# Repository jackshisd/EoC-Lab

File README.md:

| Supported Targets | ESP32 | ESP32-P4 | ESP32-S3 |
| ----------------- | ----- | -------- | -------- |

# ESP32-S3 SD + Mic + OV2640 Recorder

__WARNING:__ This project writes audio/video files to the SD card. Back up your data before testing.

Records:
- **Audio**: WAV via I2S mic (ICS-43434), `mic_0001.wav`, `mic_0002.wav`, ...
- **Contact audio**: WAV via ES8388 contact mic board, `CT0001.WAV`, `CT0002.WAV`, ...
- **Video**: MJPEG via OV2640, `VID0001.MJP`, `VID0002.MJP`, ...

Core features:
- SDMMC FAT mount/unmount
- USB MSC to expose the SD card when idle
- SSD1306 I2C OLED status
- Button UI
- BLE scan trigger (advertisements) with timestamped filenames
- Simultaneous standard mic + contact mic recording to separate WAV files
- Boot-time ES8388 codec bring-up so contact recording does not reinitialize the codec on every session

Supports SD (SDSC, SDHC, SDXC) cards and eMMC.

## Quick wiring map (ESP32-S3)

- **SD card (SDMMC):**
  - CLK: GPIO6
  - CMD: GPIO7
  - D0: GPIO5
  - D1: GPIO4
  - D2: GPIO16
  - D3: GPIO15
- **Mic (I2S):**
  - BCLK: GPIO38
  - LRCK/WS: GPIO40
  - DOUT -> ESP DIN: GPIO39
- **OLED (I2C, addr `0x3C`):**
  - SDA: GPIO1
  - SCL: GPIO2
- **Contact mic codec board (ES8388 + MCP6002):**
  - I2C SDA: GPIO1
  - I2C SCL: GPIO2
  - MCLK: GPIO41
  - ASDOUT -> ESP DIN: GPIO42
  - SCLK/BCLK: GPIO43
  - LRCK/WS: GPIO44
- **Button:**
  - GPIO45
- **Camera (OV2640):**
  - SCCB SDA: GPIO18
  - SCCB SCL: GPIO17
  - XCLK: GPIO9 (10 MHz)
  - D0..D7: GPIO47, GPIO48, GPIO14, GPIO21, GPIO12, GPIO13, GPIO10, GPIO11
  - PCLK: GPIO46
  - VSYNC: GPIO3
  - HREF: GPIO8
  - PWDN/RESET: tied in hardware (disabled in software with `-1`)

## Hardware

This project targets ESP32-S3 and uses an SD card breakout or slot, an I2S mic, an SSD1306 OLED, and an OV2640 camera.

Although it is possible to connect an SD card breakout adapter, keep in mind that connections using breakout cables are often unreliable and have poor signal integrity. You may need to use lower clock frequency when working with SD card breakout adapters.

This project doesn't utilize card detect (CD) and write protect (WP) signals from SD card slot.

### Pin assignments for ESP32

On ESP32, SDMMC peripheral is connected to specific GPIO pins using the IO MUX. GPIO pins cannot be customized. Please see the table below for the pin connections.

When using an ESP-WROVER-KIT board, this example runs without any extra modifications required. Only an SD card needs to be inserted into the slot.

ESP32 pin     | SD card pin | Notes
--------------|-------------|------------
GPIO14 (MTMS) | CLK         | 10k pullup in SD mode
GPIO15 (MTDO) | CMD         | 10k pullup in SD mode
GPIO2         | D0          | 10k pullup in SD mode, pull low to go into download mode (see Note about GPIO2 below!)
GPIO4         | D1          | not used in 1-line SD mode; 10k pullup in 4-line SD mode
GPIO12 (MTDI) | D2          | not used in 1-line SD mode; 10k pullup in 4-line SD mode (see Note about GPIO12 below!)
GPIO13 (MTCK) | D3          | not used in 1-line SD mode, but card's D3 pin must have a 10k pullup

### Pin assignments for ESP32-S3 (current project)

On ESP32-S3, SDMMC peripheral is connected to GPIO pins using GPIO matrix. This allows arbitrary GPIOs to be used to connect an SD card. In this example, GPIOs can be configured in two ways:

1. Using menuconfig: Run `idf.py menuconfig` in the project directory and open "SD/MMC Example Configuration" menu.
2. In the source code: See the initialization of `sdmmc_slot_config_t slot_config` structure in the example code.

The table below lists the default pin assignments.

When using an ESP32-S3-USB-OTG board, this example runs without any extra modifications required. Only an SD card needs to be inserted into the slot.

ESP32-S3 pin  | SD card pin | Notes
--------------|-------------|------------
GPIO6         | CLK         | 10k pullup
GPIO7         | CMD         | 10k pullup
GPIO5         | D0          | 10k pullup
GPIO4         | D1          | 10k pullup
GPIO16        | D2          | 10k pullup
GPIO15        | D3          | 10k pullup (required even in 1-line mode)

### I2S mic (ICS-43434)

ESP32-S3 pin  | Mic pin
--------------|---------
GPIO38        | BCLK/SCK
GPIO40        | WS/LRCL
GPIO39        | DOUT/SD
3.3V          | VCC
GND           | GND

SEL/LR on the mic should be tied to 3.3V (right channel), which matches the code.

### OLED (SSD1306, I2C)

ESP32-S3 pin  | OLED pin
--------------|---------
GPIO1         | SDA
GPIO2         | SCL
3.3V          | VCC
GND           | GND

I2C address is `0x3C`.

### Contact mic codec board (ES8388)

ESP32-S3 pin  | Contact mic board pin
--------------|----------------------
GPIO1         | CDATA / I2C SDA
GPIO2         | CCLK / I2C SCL
GPIO41        | MCLK
GPIO42        | ASDOUT / codec data out
GPIO43        | SCLK / BCLK
GPIO44        | LRCK / WS
3.3V          | Codec supply
GND           | GND

Current firmware behavior:

- The ES8388 codec is initialized once at boot.
- If codec init is slow, the OLED shows retry/progress messages during boot.
- Once the OLED shows `codec ok`, normal operation begins.
- Later recordings reuse the initialized codec instead of re-running full codec init every time.

### Camera (OV2640, Waveshare) — read this first

This project uses OV2640 over SCCB (I2C). The camera is sensitive to pin choice and initial frames are often corrupted.

**Current working pin map (ESP32-S3 custom board):**

ESP32-S3 pin | OV2640 pin | Notes
-------------|------------|------
GPIO18       | SCCB SDA   | Camera I2C data
GPIO17       | SCCB SCL   | Camera I2C clock
GPIO9        | XCLK       | External clock (10 MHz)
GPIO47       | D0         | Data bit 0
GPIO48       | D1         | Data bit 1
GPIO14       | D2         | Data bit 2
GPIO21       | D3         | Data bit 3
GPIO12       | D4         | Data bit 4
GPIO13       | D5         | Data bit 5
GPIO10       | D6         | Data bit 6
GPIO11       | D7         | Data bit 7
GPIO46       | PCLK       | Pixel clock
GPIO3        | VSYNC      | Frame sync
GPIO8        | HREF       | Line sync

PWDN and RESET are tied in hardware (PWDN -> GND, RESET -> 3.3V). In software, they are disabled (set to `-1`).

**What was broken and how it was fixed:**

- Camera capture initially failed because of a real solder bridge between `VSYNC` and `PCLK`.
  Fix: remove the bridge; camera now initializes and produces frames.
- OLED instability was partly caused by a pin conflict: OLED `SCL` and the buzzer both used GPIO2.
  Fix: remove all buzzer code so GPIO2 is dedicated to OLED `SCL`.
- Mic audio was silent with one mic connected because the code was reading the wrong I2S slot.
  Fix: switch the mic capture to the right channel and wire the mic `SEL/LR` pin high.
- FATFS without LFN rejects long filenames.
  Fix: keep video filenames 8.3-safe as `VID0001.MJP` and BLE timestamped names as `MMDDHHMM.MJP` / `MMDDHHMM.WAV`.

**Playback note:** `VIDxxxx.MJP` is a raw MJPEG stream (not a container). VLC can play it; for QuickTime, convert to AVI/MP4.

**Current camera behavior:**

- Video recording is capped in software at `10 FPS` to reduce camera/SD load and improve stability.

### BLE trigger and timestamped filenames

The device scans BLE advertisements and uses a UUID-encoded timestamp to name files:

- **Video:** `MMDDHHMM.MJP`
- **Audio:** `MMDDHHMM.WAV`
- **Contact audio:** a contact-mic WAV derived from the same BLE timestamp, with the first timestamp character replaced by `C` to stay 8.3-safe

If no valid BLE timestamp is seen, it falls back to the index names:

- `VID0001.MJP`
- `mic_0001.wav`
- `CT0001.WAV`

**UUID format (128-bit):** `00000000-0000-0000-TT00-YYMMDDHHMMSS`

- Prefix is fixed: all zeroes (`00 00 00 00 00 00 00 00`)
- `TT` = `01` short press, `02` long press
- `YYMMDDHHMMSS` are BCD digits (base-10 nibbles)
- Filenames use `MMDDHHMM` to stay 8.3-safe

**Current BLE scan behavior:**

- BLE trigger scanning is enabled.
- Scanning is passive with duplicate filtering disabled.
- Scan duty cycle was reduced from continuous `10 ms / 10 ms` (~100%) to `5 ms / 80 ms` (~6.25%) to reduce radio and power load while keeping start/stop trigger support during recording.

### Button

ESP32-S3 pin  | Device
--------------|---------
GPIO45        | Button (pull-up input)

### Pin assignments for ESP32-P4

On ESP32-P4, Slot 1 of the SDMMC peripheral is connected to GPIO pins using GPIO matrix. This allows arbitrary GPIOs to be used to connect an SD card. In this example, GPIOs can be configured in two ways:

1. Using menuconfig: Run `idf.py menuconfig` in the project directory and open `SD/MMC Example Configuration` menu.
2. In the source code: See the initialization of `sdmmc_slot_config_t slot_config` structure in the example code.

The table below lists the default pin assignments.

ESP32-P4 pin  | SD card pin | Notes
--------------|-------------|------------
GPIO43        | CLK         | 10k pullup
GPIO44        | CMD         | 10k pullup
GPIO39        | D0          | 10k pullup
GPIO40        | D1          | not used in 1-line SD mode; 10k pullup in 4-line mode
GPIO41        | D2          | not used in 1-line SD mode; 10k pullup in 4-line mode
GPIO42        | D3          | not used in 1-line SD mode, but card's D3 pin must have a 10k pullup

Default dedicated pins on ESP32-P4 are able to connect to an ultra high-speed SD card (UHS-I) which requires 1.8V switching (instead of the regular 3.3V). This means the user has to provide an external LDO power supply to use them, or to enable and configure an internal LDO via `idf.py menuconfig` -> `SD/MMC Example Configuration` -> `SD power supply comes from internal LDO IO`.

When using different GPIO pins this is not required and `SD power supply comes from internal LDO IO` setting can be disabled.

### 4-line and 1-line SD modes

By default, this example uses 4 line SD mode, utilizing 6 pins: CLK, CMD, D0 - D3. It is possible to use 1-line mode (CLK, CMD, D0) by changing "SD/MMC bus width" in the example configuration menu (see `CONFIG_EXAMPLE_SDMMC_BUS_WIDTH_1`).

Note that even if card's D3 line is not connected to the ESP chip, it still has to be pulled up, otherwise the card will go into SPI protocol mode.

### Note about GPIO2 (ESP32 only)

GPIO2 pin is used as a bootstrapping pin, and should be low to enter UART download mode. One way to do this is to connect GPIO0 and GPIO2 using a jumper, and then the auto-reset circuit on most development boards will pull GPIO2 low along with GPIO0, when entering download mode.

- Some boards have pulldown and/or LED on GPIO2. LED is usually ok, but pulldown will interfere with D0 signals and must be removed. Check the schematic of your development board for anything connected to GPIO2.

### Note about GPIO12 (ESP32 only)

GPIO12 is used as a bootstrapping pin to select output voltage of an internal regulator which powers the flash chip (VDD_SDIO). This pin has an internal pulldown so if left unconnected it will read low at reset (selecting default 3.3V operation). When adding a pullup to this pin for SD card operation, consider the following:

- For boards which don't use the internal regulator (VDD_SDIO) to power the flash, GPIO12 can be pulled high.
- For boards which use 1.8V flash chip, GPIO12 needs to be pulled high at reset. This is fully compatible with SD card operation.
- On boards which use the internal regulator and a 3.3V flash chip, GPIO12 must be low at reset. This is incompatible with SD card operation.
    * In most cases, external pullup can be omitted and an internal pullup can be enabled using a `gpio_pullup_en(GPIO_NUM_12);` call. Most SD cards work fine when an internal pullup on GPIO12 line is enabled. Note that if ESP32 experiences a power-on reset while the SD card is sending data, high level on GPIO12 can be latched into the bootstrapping register, and ESP32 will enter a boot loop until external reset with correct GPIO12 level is applied.
    * Another option is to burn the flash voltage selection efuses. This will permanently select 3.3V output voltage for the internal regulator, and GPIO12 will not be used as a bootstrapping pin. Then it is safe to connect a pullup resistor to GPIO12. This option is suggested for production use.

The following command can be used to program flash voltage selection efuses **to 3.3V**:

```sh
    espefuse.py set_flash_voltage 3.3V
```

This command will burn the `XPD_SDIO_TIEH`, `XPD_SDIO_FORCE`, and `XPD_SDIO_REG` efuses. With all three burned to value 1, the internal VDD_SDIO flash voltage regulator is permanently enabled at 3.3V. See the technical reference manual for more details.

`espefuse.py` has a `--do-not-confirm` option if running from an automated flashing script.

See [the document about pullup requirements](https://docs.espressif.com/projects/esp-idf/en/latest/api-reference/peripherals/sd_pullup_requirements.html) for more details about pullup support and compatibility of modules and development boards.

## How to use

### Build and flash

Build the project and flash it to the board, then run monitor tool to view serial output:

```
idf.py -p PORT flash monitor
```

(Replace PORT with serial port name.)

(To exit the serial monitor, type ``Ctrl-]``.)

### Recording flow

1. Long press starts recording. USB MSC is stopped and the SD card is mounted to the app.
2. The normal I2S mic and the ES8388 contact mic are both recorded at the same time into separate WAV files.
3. Video is recorded in parallel if the camera is enabled and initialized.
4. Long press again stops recording, finalizes the WAV header(s), waits for the camera task to stop, and returns the SD card to USB MSC.
5. A later long press repeats the cycle with a new filename set.

### Idle / post-record OLED messages

The OLED status is more specific than a generic `Ready` screen:

- Clean success: `Recorded Xs at` + the standard mic filename
- Standard mic file exists even if the task reported a higher-level failure: `Mic file saved`
- Standard mic saved but contact mic failed: `Mic saved; c fail`
- Startup codec bring-up: retry/progress messages followed by `codec ok`

Short press toggles pause/resume during recording.

### SD card mount warnings

If SD mounting fails or is not ready, the OLED shows a warning:

- `SD init failed`
- `SD mount failed`
- `SD not ready`

When these appear, re-seat the SD card and try again. Also wait for the
`Exposing SD card over USB` log before unplugging or copying files.

See the Getting Started Guide for full steps to configure and use ESP-IDF to build projects.

### USB mass storage

When idle, the SD card is exposed over USB MSC for file access from your computer.
During recording, USB MSC is stopped and the SD card is mounted to the application.
After recording finishes, USB MSC is restarted and the card is visible again on the host.

## Example output

Here is an example console output. In this case a 128MB SDSC card was connected, and `EXAMPLE_FORMAT_IF_MOUNT_FAILED` menuconfig option enabled. Card was unformatted, so the initial mount has failed. Card was then partitioned, formatted, and mounted again.

```
I (336) example: Initializing SD card
I (336) example: Using SDMMC peripheral
I (420) example: Mounting filesystem
I (538) mic: Waiting for long press
I (1840) button: Recording started
I (1841) mic: Recording started
I (9620) mic: Stop requested
I (9622) mic: Captured 7 sec to /sdcard/mic_0001.wav
I (9660) example: Card unmounted
```

## Troubleshooting

### Failure to download the example

```
Connecting........_____....._____....._____....._____....._____....._____....._____

A fatal error occurred: Failed to connect to Espressif device: Invalid head of packet (0x34)
```

Disconnect the SD card D0/MISO line from GPIO2 and try uploading again. Read "Note about GPIO2" above.

### Card fails to initialize with `sdmmc_init_sd_scr: send_scr (1) returned 0x107` error

Check connections between the card and the ESP32. For example, if you have disconnected GPIO2 to work around the flashing issue, connect it back and reset the ESP32 (using a button on the development board, or by pressing Ctrl-T Ctrl-R in IDF Monitor).

### Card fails to initialize with `sdmmc_check_scr: send_scr returned 0xffffffff` error

Connections between the card and the ESP32 are too long for the frequency used. Try using shorter connections, or try reducing the clock speed of SD interface.

### Failure to mount filesystem

```
example: Failed to mount filesystem. If you want the card to be formatted, set the EXAMPLE_FORMAT_IF_MOUNT_FAILED menuconfig option.
```
The example will be able to mount only cards formatted using FAT32 filesystem. If the card is formatted as exFAT or some other filesystem, you have an option to format it in the example code. Enable the `EXAMPLE_FORMAT_IF_MOUNT_FAILED` menuconfig option, then build and flash the example.

### Debug SD connections and pullup strength

> If the initialization of the SD card fails, initially follow the above options. If the issue persists, confirm the connection of pullups to the SD pins. To do this, enable the` Debug sd pin connections and pullup strength` option from menuconfig and rerun the code. This will provide the following result:

```
**** PIN recovery time ****

PIN 14 CLK  10044 cycles
PIN 15 CMD  10034 cycles
PIN  2  D0  10034 cycles
PIN  4  D1  10034 cycles
PIN 12  D2  10034 cycles
PIN 13  D3  10034 cycles

**** PIN recovery time with weak pullup ****

PIN 14 CLK  100 cycles
PIN 15 CMD  100 cycles
PIN  2  D0  100 cycles
PIN  4  D1  100 cycles
PIN 12  D2  100 cycles
PIN 13  D3  100 cycles

**** PIN voltage levels ****

PIN 14 CLK  0.6V
PIN 15 CMD  0.3V
PIN  2  D0  0.8V
PIN  4  D1  0.6V
PIN 12  D2  0.4V
PIN 13  D3  0.8V

**** PIN voltage levels with weak pullup ****

PIN 14 CLK  1.0V
PIN 15 CMD  1.1V
PIN  2  D0  1.0V
PIN  4  D1  1.0V
PIN 12  D2  1.0V
PIN 13  D3  1.2V

**** PIN cross-talk ****

              CLK   CMD    D0    D1    D2    D3
PIN 14 CLK     --   0.2V  0.1V  0.1V  0.1V  0.2V
PIN 15 CMD    0.1V   --   0.1V  0.1V  0.1V  0.1V
PIN  2  D0    0.1V  0.1V   --   0.2V  0.1V  0.1V
PIN  4  D1    0.1V  0.1V  0.3V   --   0.1V  0.1V
PIN 12  D2    0.1V  0.2V  0.2V  0.1V   --   0.1V
PIN 13  D3    0.1V  0.2V  0.1V  0.1V  0.1V   --

**** PIN cross-talk with weak pullup ****

              CLK   CMD    D0    D1    D2    D3
PIN 14 CLK     --   1.0V  1.0V  1.0V  1.0V  1.2V
PIN 15 CMD    0.9V   --   1.0V  1.0V  1.0V  1.2V
PIN  2  D0    0.9V  1.0V   --   1.0V  1.0V  1.2V
PIN  4  D1    0.9V  1.0V  1.2V   --   1.0V  1.2V
PIN 12  D2    0.9V  1.1V  1.2V  0.9V   --   1.2V
PIN 13  D3    0.9V  1.2V  1.1V  0.9V  0.9V   --
I (845) main_task: Returned from app_main()
```

In the absence of connected pullups and having the weak pullups enabled, you can assess the pullup connections by comparing PIN recovery time measured in CPU cycles. To check pullup connections, configure the pin as open drain, set it to low state, and count the cpu cycles consumed before returning to high state. If a pullup is connected, the pin will get back to high state after reasonably small cycle count, typically around 50-300 cycles, depending on pullup strength. If no pullup is connected, the PIN stays low and the measurement times out after 10000 cycles.

It will also provide the voltage levels at the corresponding SD pins. By default, this information is provided for ESP32 chip only, and for other chipsets, verify the availability of ADC pins for the respective GPIO using [this](https://docs.espressif.com/projects/esp-idf/en/latest/esp32/api-reference/peripherals/gpio.html#gpio-summary) and configure ADC mapped pins using menuconfig. Then test the voltage levels accordingly.

You can monitor the voltage levels of individual pins using `PIN voltage levels` and `PIN voltage levels with weak pullup`. However, if one pin being pulled low and experiencing interference with another pin, you can detect it through `PIN cross-talk` and `PIN cross-talk with weak pullup`. In the absence of pullups, voltage levels at each pin should range from 0 to 0.3V. With 10k pullups connected, the voltage will be between 3.1V to 3.3V, contingent on the connection between ADC pins and SD pins, and with weak pullups connected, it can fluctuate between 0.8V to 1.2V, depending on pullup strength.
>>>>>>> 207d2c1 (Initial commit)

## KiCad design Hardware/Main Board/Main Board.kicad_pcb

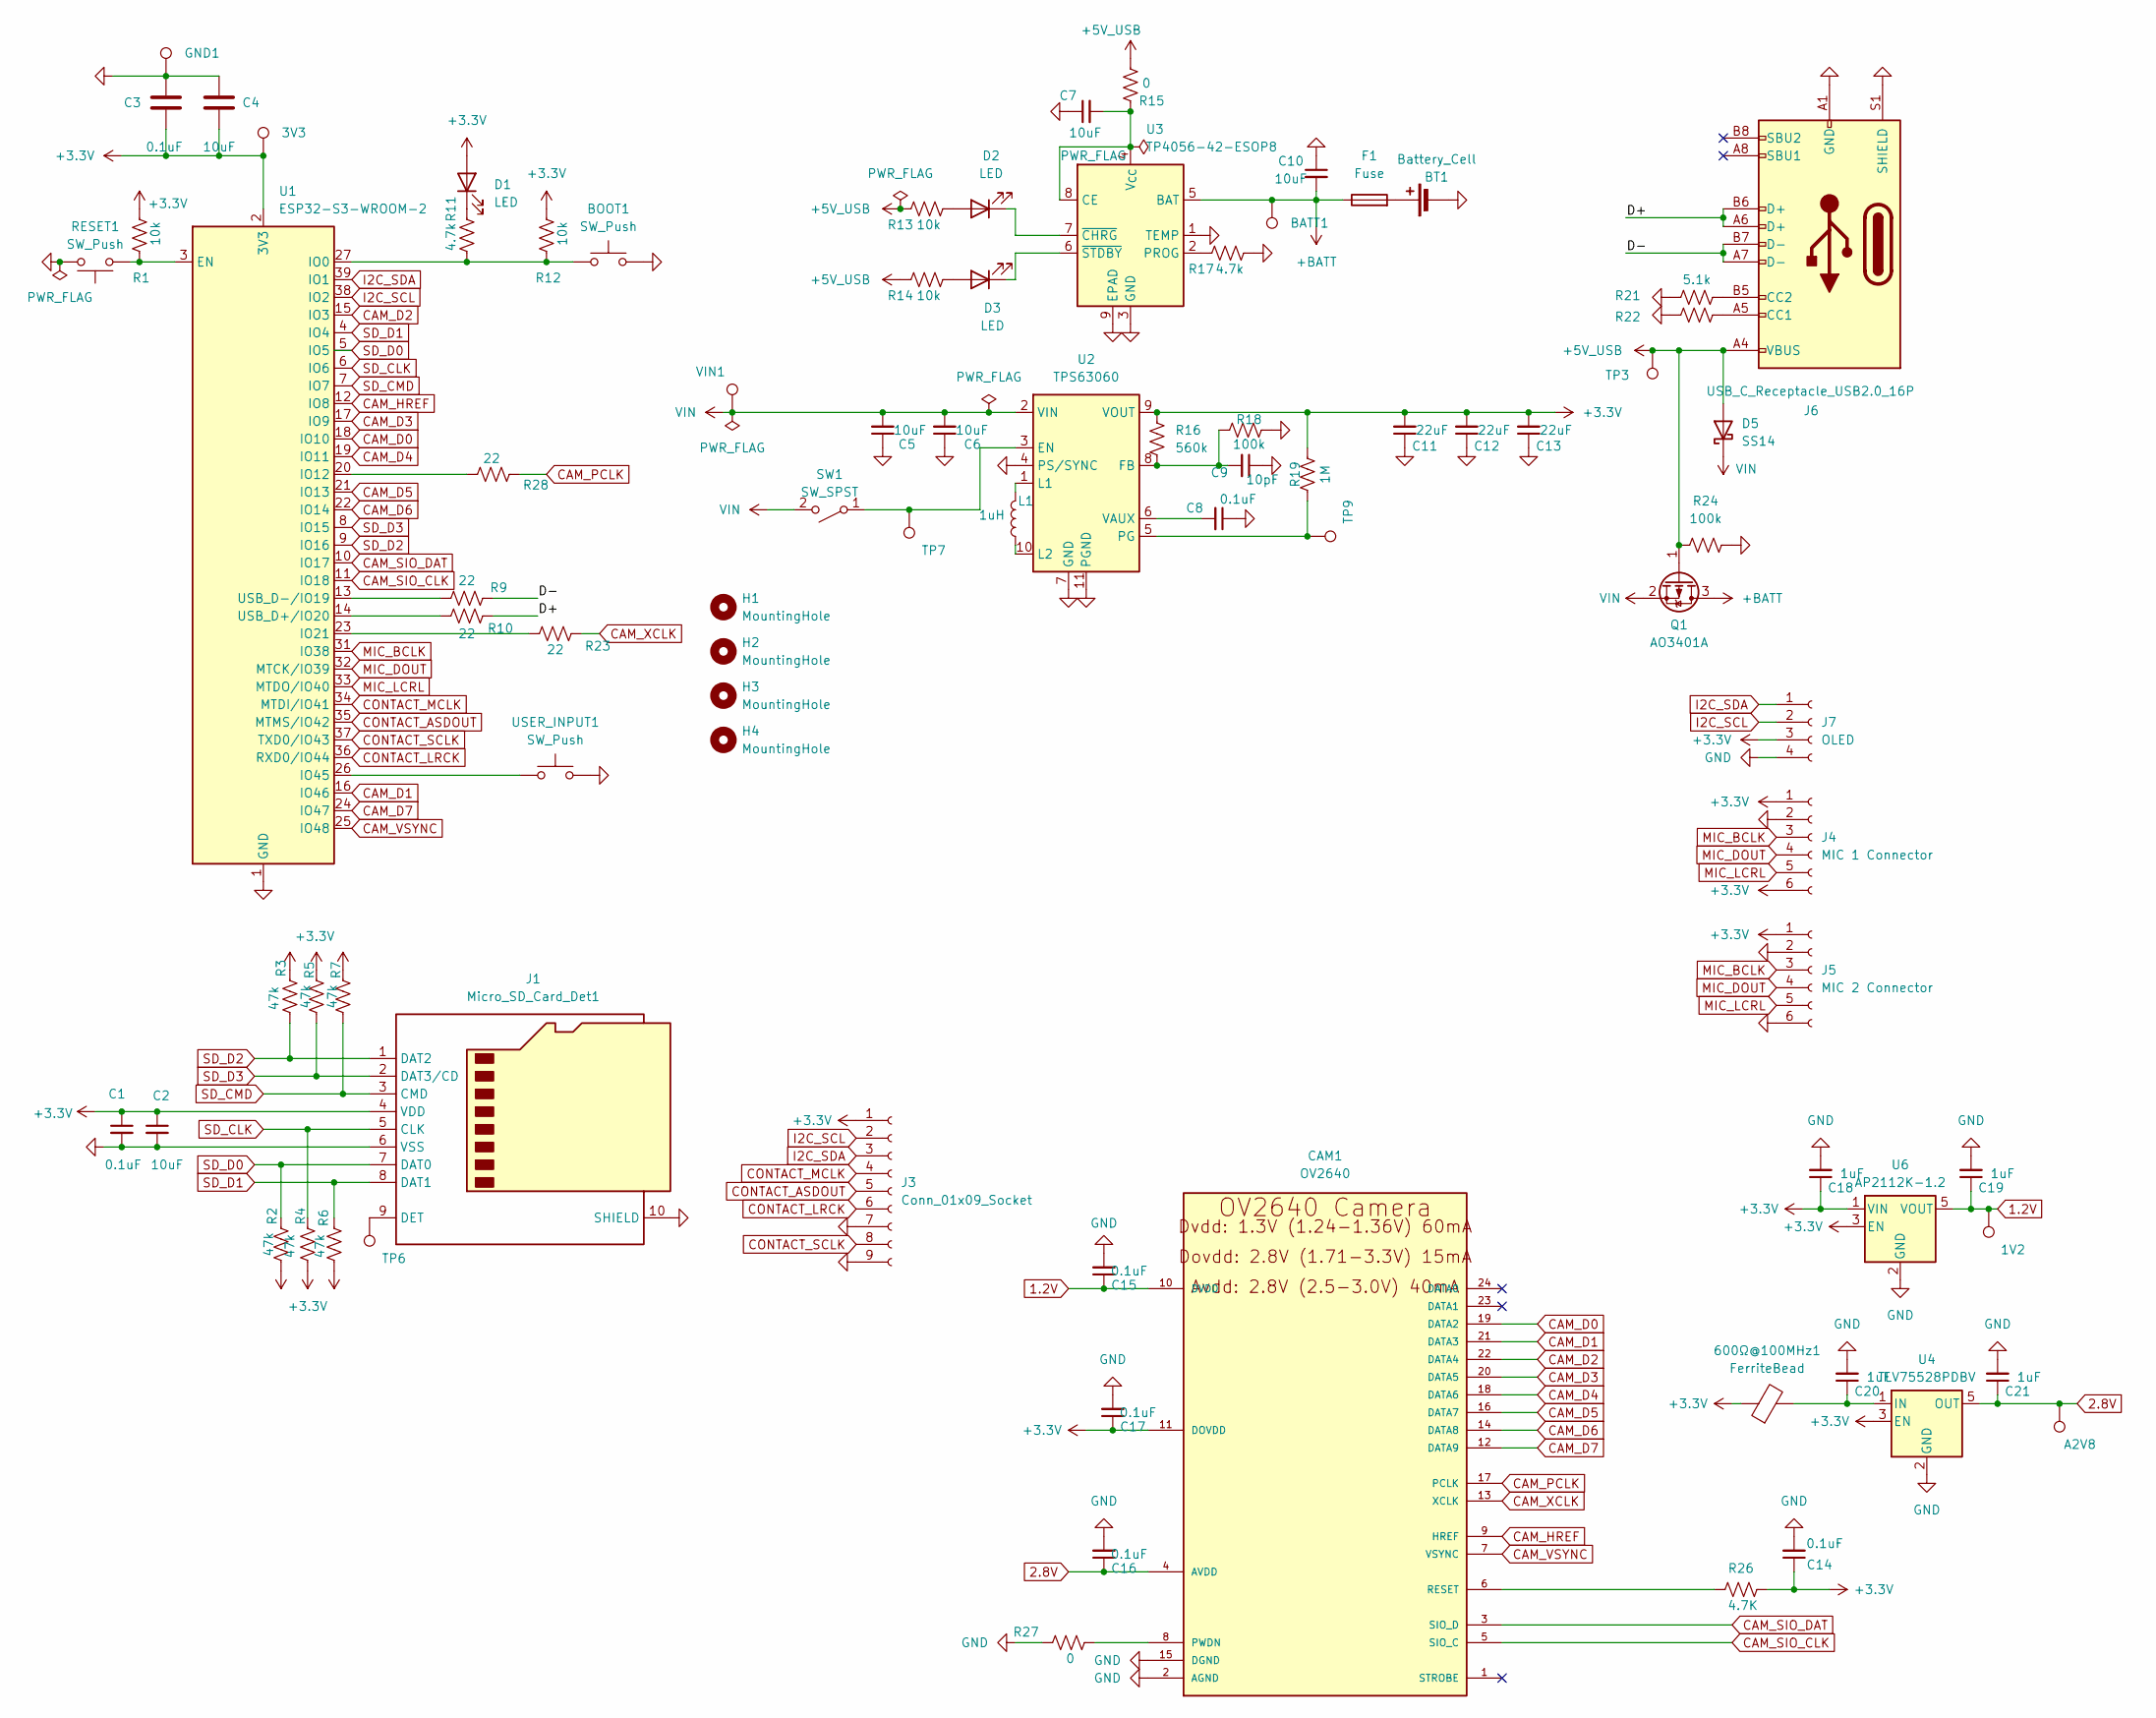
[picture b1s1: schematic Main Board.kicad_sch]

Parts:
1V2: TestPoint; TestPoint_Pad_1.0x1.0mm
3V3: TestPoint; PinHeader_1x01_P2.54mm_Vertical
600Ω@100MHz1: FerriteBead; R_0603_1608Metric
A2V8: TestPoint; TestPoint_Pad_1.0x1.0mm
BATT1: TestPoint; TestPoint_Pad_1.0x1.0mm
BOOT1: SW_Push; SW_SPST_TL3342
BT1: Battery_Cell; JST_PH_S2B-PH-K_1x02_P2.00mm_Horizontal
C1, C3, C8: 0.1uF; C_0402_1005Metric
C2, C7, C10: 10uF; C_0402_1005Metric
C4, C5, C6: 10uF; C_0603_1608Metric
C9: 10pF; C_0402_1005Metric
C11, C12, C13: 22uF; C_0805_2012Metric
C14, C15, C16, C17: 0.1uF; C_0603_1608Metric
C18, C19, C20, C21: 1uF; C_0603_1608Metric
CAM1: OV2640
D1: LED; PinHeader_1x02_P2.54mm_Vertical
D2, D3: LED; LED_0603_1608Metric
D5: SS14; D_SMA
F1: Fuse; Fuse_1206_3216Metric
GND1: TestPoint; PinHeader_1x01_P2.54mm_Vertical
H1, H2, H3, H4: MountingHole; MountingHole_2.1mm
J1: Micro_SD_Card_Det1; microSD_HC_Molex_104031-0811
J3: Conn_01x09_Socket; JST_GH_SM09B-GHS-TB_1x09-1MP_P1.25mm_Horizontal
J4: MIC 1 Connector; JST_GH_SM06B-GHS-TB_1x06-1MP_P1.25mm_Horizontal
J5: MIC 2 Connector; JST_GH_SM06B-GHS-TB_1x06-1MP_P1.25mm_Horizontal
J6: USB_C_Receptacle_USB2.0_16P; USB_C_Receptacle_HRO_TYPE-C-31-M-12
J7: OLED; PinHeader_1x04_P2.54mm_Vertical
L1: 1uH; L_Bourns-SRN4018
Q1: AO3401A; SOT-23
R1, R12, R13, R14: 10k; R_0402_1005Metric
R2, R3, R4, R5, R6, R7: 47k; R_0402_1005Metric
R9, R10, R23, R28: 22; R_0402_1005Metric
R11, R17: 4.7k; R_0402_1005Metric
R15, R27: 0; R_0402_1005Metric
R16: 560k; R_0402_1005Metric
R18, R24: 100k; R_0402_1005Metric
R19: 1M; R_0402_1005Metric
R21, R22: 5.1k; R_0402_1005Metric
R26: 4.7K; R_0402_1005Metric
RESET1: SW_Push; SW_SPST_TL3342
SW1: SW_SPST; PinHeader_1x03_P2.54mm_Vertical
TP3: TestPoint; PinHeader_1x01_P2.54mm_Vertical
TP6, TP7, TP9: TestPoint; TestPoint_Pad_1.0x1.0mm
U1: ESP32-S3-WROOM-2
U2: TPS63060; Texas_S-PWSON-N10_ThermalVias
U3: TP4056-42-ESOP8; SOIC-8-1EP_3.9x4.9mm_P1.27mm_EP2.41x3.3mm_ThermalVias
U4: TLV75528PDBV; SOT-23-5
U6: AP2112K-1.2; SOT-23-5
USER_INPUT1: SW_Push; SW_SPST_TL3342
VIN1: TestPoint; TestPoint_Pad_1.0x1.0mm

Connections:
1.2V: 1V2.1, C15.1, C19.1, CAM1.10 (DVDD), U6.5 (VOUT)
2.8V: A2V8.1, C16.1, C21.1, CAM1.4 (AVDD), U4.5 (OUT)
+3.3V: 3V3.1, 600Ω@100MHz1.1, C1.1, C2.1, C3.2, C4.1, C11.2, C12.2, C13.2, C14.1, C17.1, C18.1, CAM1.11 (DOVDD), D1.2 (A), J1.4 (VDD), J3.1, J4.1, J4.6, J5.1, J7.3, R1.1, R2.1, R3.2, R4.1, R5.2, R6.1, R7.2, R12.1, R16.2, R19.2, R26.1, U1.2 (3V3), U2.9 (VOUT), U4.3 (EN), U6.1 (VIN), U6.3 (EN)
+5V_USB: D5.2 (A), J6.A4 (VBUS), J6.A9 (VBUS), J6.B4 (VBUS), J6.B9 (VBUS), Q1.1 (G), R13.2, R14.2, R15.1, R24.1, TP3.1
+BATT: BATT1.1, C10.2, F1.1, Q1.3 (D), U3.5 (BAT)
/D+: J6.A6 (D+), J6.B6 (D+), R10.1
/D-: J6.A7 (D-), J6.B7 (D-), R9.1
CAM_D0: CAM1.19 (DATA2), U1.18 (IO10)
CAM_D1: CAM1.21 (DATA3), U1.16 (IO46)
CAM_D2: CAM1.22 (DATA4), U1.15 (IO3)
CAM_D3: CAM1.20 (DATA5), U1.17 (IO9)
CAM_D4: CAM1.18 (DATA6), U1.19 (IO11)
CAM_D5: CAM1.16 (DATA7), U1.21 (IO13)
CAM_D6: CAM1.14 (DATA8), U1.22 (IO14)
CAM_D7: CAM1.12 (DATA9), U1.24 (IO47)
CAM_HREF: CAM1.9 (HREF), U1.12 (IO8)
CAM_PCLK: CAM1.17 (PCLK), R28.2
CAM_SIO_CLK: CAM1.5 (SIO_C), U1.11 (IO18)
CAM_SIO_DAT: CAM1.3 (SIO_D), U1.10 (IO17)
CAM_VSYNC: CAM1.7 (VSYNC), U1.25 (IO48)
CAM_XCLK: CAM1.13 (XCLK), R23.2
CONTACT_ASDOUT: J3.5, U1.35 (MTMS/IO42)
CONTACT_LRCK: J3.6, U1.36 (RXD0/IO44)
CONTACT_MCLK: J3.4, U1.34 (MTDI/IO41)
CONTACT_SCLK: J3.8, U1.37 (TXD0/IO43)
GND: BOOT1.2, BT1.2 (-), C1.2, C2.2, C3.1, C4.2, C5.1, C6.1, C7.1, C8.1, C9.1, C10.1, C11.1, C12.1, C13.1, C14.2, C15.2, C16.2, C17.2, C18.2, C19.2, C20.2, C21.2, CAM1.2 (AGND), CAM1.15 (DGND), CAM1.MT1 (DGND), CAM1.MT2 (DGND), GND1.1, J1.6 (VSS), J1.10 (SHIELD), J3.7, J3.9, J4.2, J5.2, J5.6, J6.A1 (GND), J6.A12 (GND), J6.B1 (GND), J6.B12 (GND), J6.S1 (SHIELD), J7.4, R17.1, R18.1, R21.2, R22.2, R24.2, R27.2, RESET1.2, U1.1 (GND), U1.40 (GND), U1.41 (GND), U2.4 (PS/SYNC), U2.7 (GND), U2.11 (PGND), U3.1 (TEMP), U3.3 (GND), U3.9 (EPAD), U4.2 (GND), U6.2 (GND), USER_INPUT1.2
I2C_SCL: J3.2, J7.2, U1.38 (IO2)
I2C_SDA: J3.3, J7.1, U1.39 (IO1)
MIC_BCLK: J4.3, J5.3, U1.31 (IO38)
MIC_DOUT: J4.4, J5.4, U1.32 (MTCK/IO39)
MIC_LCRL: J4.5, J5.5, U1.33 (MTDO/IO40)
unnamed: BT1.1 (+), F1.2
unnamed: CAM1.8 (PWDN), R27.1
unnamed: CAM1.6 (RESET), R26.2
unnamed: D1.1 (K), R11.2
unnamed: D2.2 (A), R13.1
unnamed: D2.1 (K), U3.7 (~CHRG)
unnamed: D3.2 (A), R14.1
unnamed: D3.1 (K), U3.6 (~STDBY)
unnamed: J1.9 (DET), TP6.1
unnamed: J6.A5 (CC1), R22.1
unnamed: J6.B5 (CC2), R21.1
unnamed: SW1.1 (A), TP7.1, U2.3 (EN)
unnamed: R1.2, RESET1.1, U1.3 (EN)
unnamed: BOOT1.1, R11.1, R12.2, U1.27 (IO0)
unnamed: R28.1, U1.20 (IO12)
unnamed: R23.1, U1.23 (IO21)
unnamed: U1.26 (IO45), USER_INPUT1.1
unnamed: R10.2, U1.14 (USB_D+/IO20)
unnamed: R9.2, U1.13 (USB_D-/IO19)
unnamed: C9.2, R16.1, R18.2, U2.8 (FB)
unnamed: L1.2, U2.1 (L1)
unnamed: L1.1, U2.10 (L2)
unnamed: R19.1, TP9.1, U2.5 (PG)
unnamed: C8.2, U2.6 (VAUX)
unnamed: C7.2, R15.2, U3.4 (V_{CC}), U3.8 (CE)
unnamed: R17.2, U3.2 (PROG)
unnamed: 600Ω@100MHz1.2, C20.1, U4.1 (IN)
SD_CLK: J1.5 (CLK), R4.2, U1.6 (IO6)
SD_CMD: J1.3 (CMD), R7.1, U1.7 (IO7)
SD_D0: J1.7 (DAT0), R2.2, U1.5 (IO5)
SD_D1: J1.8 (DAT1), R6.2, U1.4 (IO4)
SD_D2: J1.1 (DAT2), R3.1, U1.9 (IO16)
SD_D3: J1.2 (DAT3/CD), R5.1, U1.8 (IO15)
VIN: C5.2, C6.2, D5.1 (K), Q1.2 (S), SW1.2 (B), U2.2 (VIN), VIN1.1

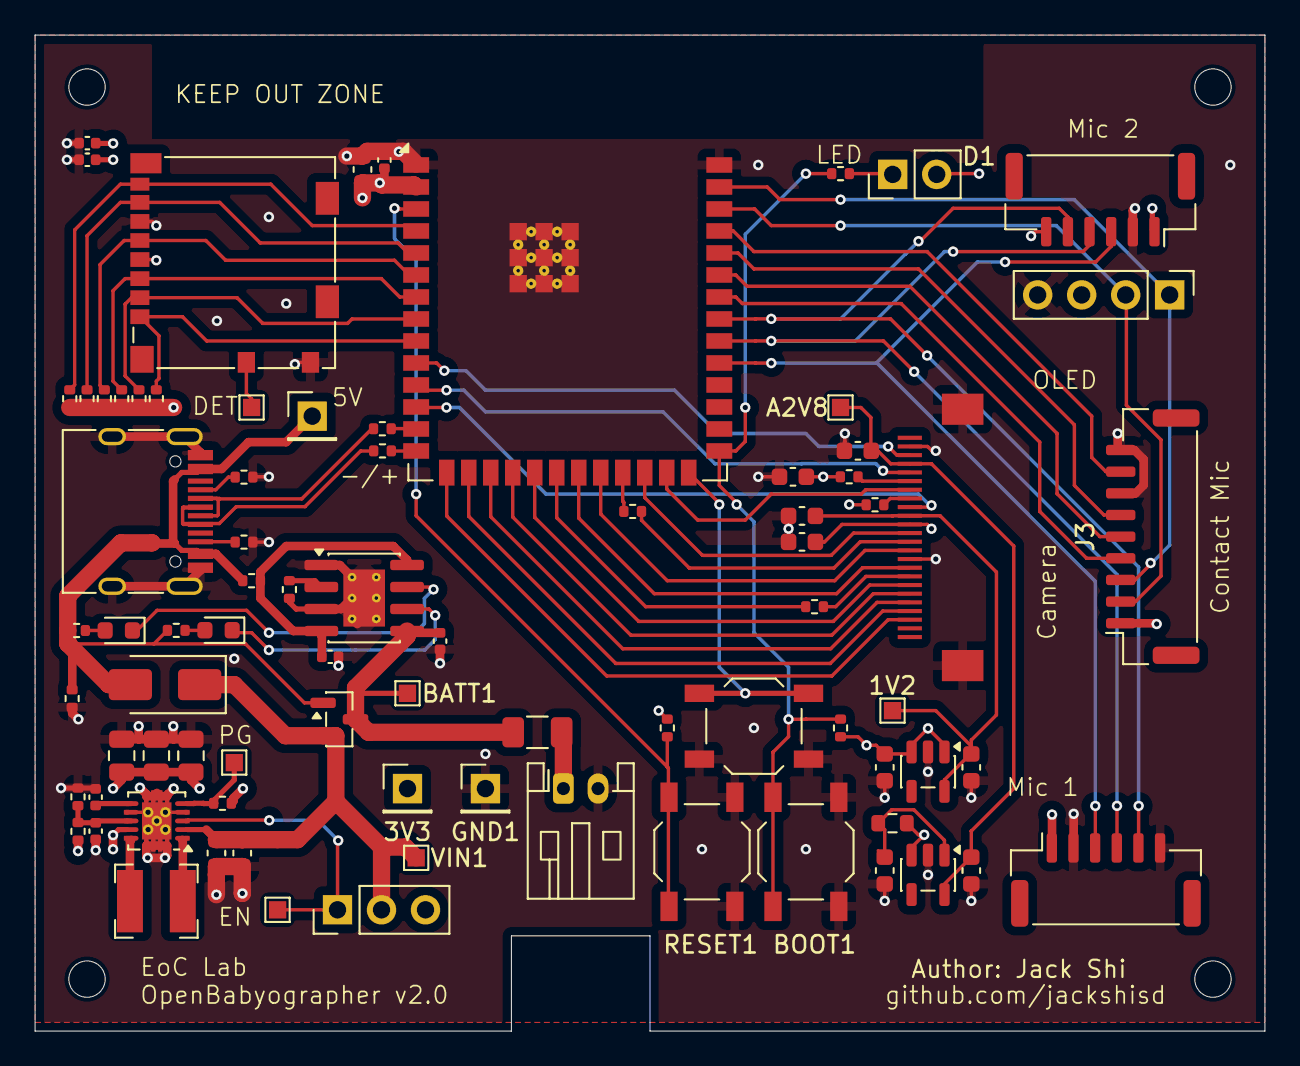
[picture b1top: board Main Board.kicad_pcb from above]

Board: 4 copper layers, 71.0 x 57.5 mm, 85 parts (0 on the bottom side), 65 nets.

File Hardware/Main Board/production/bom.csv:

Designator,Footprint,Quantity,Value,LCSC Part #
"1V2, A2V8, BATT1, TP6, TP7, TP9, VIN1",TestPoint_Pad_1.0x1.0mm,7,TestPoint,
"3V3, GND1, TP3",PinHeader_1x01_P2.54mm_Vertical,3,TestPoint,
600Ω@100MHZ1,0603,1,FerriteBead,
"BOOT1, RESET1, USER_INPUT1",SW_SPST_TL3342,3,SW_Push,
BT1,JST_PH_S2B-PH-K_1x02_P2.00mm_Horizontal,1,Battery_Cell,
"C1, C3, C8",0402,3,0.1uF,
"C10, C2, C7",0402,3,10uF,
"C11, C12, C13",0805,3,22uF,
"C14, C15, C16, C17",0603,4,0.1uF,
"C18, C19, C20, C21",0603,4,1uF,
"C4, C5, C6",0603,3,10uF,
C9,0402,1,10pF,
CAM1,OV2640,1,OV2640,
D1,PinHeader_1x02_P2.54mm_Vertical,1,LED,
"D2, D3",0603,2,LED,
D5,D_SMA,1,SS14,
F1,1206,1,Fuse,
J1,microSD_HC_Molex_104031-0811,1,Micro_SD_Card_Det1,
J3,JST_GH_SM09B-GHS-TB_1x09-1MP_P1.25mm_Horizontal,1,Conn_01x09_Socket,
J4,JST_GH_SM06B-GHS-TB_1x06-1MP_P1.25mm_Horizontal,1,MIC 1 Connector,
J5,JST_GH_SM06B-GHS-TB_1x06-1MP_P1.25mm_Horizontal,1,MIC 2 Connector,
J6,USB_C_Receptacle_HRO_TYPE-C-31-M-12,1,USB_C_Receptacle_USB2.0_16P,
J7,PinHeader_1x04_P2.54mm_Vertical,1,OLED,
L1,L_Bourns-SRN4018,1,1uH,
Q1,SOT-23,1,AO3401A,
"R1, R12, R13, R14",0402,4,10k,
"R10, R23, R28, R9",0402,4,22,
"R11, R17, R26",0402,3,4.7k,
"R15, R27",0402,2,0,
R16,0402,1,560k,
"R18, R24",0402,2,100k,
R19,0402,1,1M,
"R2, R3, R4, R5, R6, R7",0402,6,47k,
"R21, R22",0402,2,5.1k,
SW1,PinHeader_1x03_P2.54mm_Vertical,1,SW_SPST,
U1,ESP32-S3-WROOM-2,1,ESP32-S3-WROOM-2,
U2,Texas_S-PWSON-N10_ThermalVias,1,TPS63060,
U3,SOIC-8-1EP_3.9x4.9mm_P1.27mm_EP2.41x3.3mm_ThermalVias,1,TP4056-42-ESOP8,
U4,SOT-23-5,1,TLV75528PDBV,
U6,SOT-23-5,1,AP2112K-1.2,

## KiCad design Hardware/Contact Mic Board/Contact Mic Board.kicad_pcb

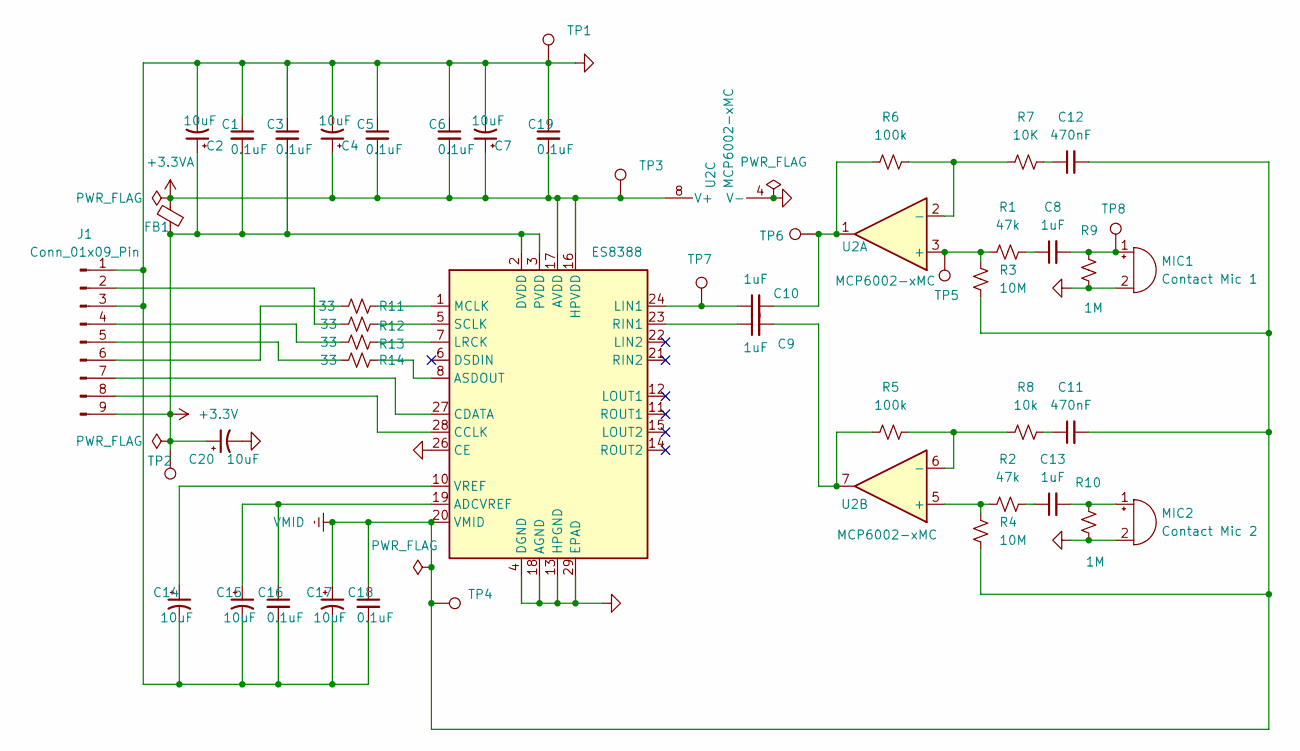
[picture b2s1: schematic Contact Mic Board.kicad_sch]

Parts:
C1, C3, C5, C6, C16, C18, C19: 0.1uF; C_0402_1005Metric
C2, C4, C7, C14, C15, C17, C20: 10uF; C_0402_1005Metric
C8, C9, C10, C13: 1uF; C_0402_1005Metric
C11, C12: 470nF; C_0402_1005Metric
FB1: FerriteBead_Small; C_0603_1608Metric
J1: Conn_01x09_Pin; JST_GH_SM09B-GHS-TB_1x09-1MP_P1.25mm_Horizontal
MIC1: Contact Mic 1; PinHeader_1x02_P2.54mm_Vertical
MIC2: Contact Mic 2; PinHeader_1x02_P2.54mm_Vertical
R1, R2: 47k; C_0402_1005Metric
R3, R4: 10M; C_0402_1005Metric
R5, R6: 100k; D_0805_2012Metric_Pad1.15x1.40mm_HandSolder
R7: 10K; C_0402_1005Metric
R8: 10k; C_0402_1005Metric
R9, R10: 1M; C_0402_1005Metric
R11, R12, R13, R14: 33; C_0402_1005Metric
TP1, TP2, TP3, TP4, TP5, TP6, TP7, TP8: TestPoint; TestPoint_Pad_1.0x1.0mm
U1: ES8388; QFN-28-1EP_4x4mm_P0.45mm_EP2.6x2.6mm
U2: MCP6002-xMC; DFN-8-1EP_3x2mm_P0.5mm_EP1.75x1.45mm

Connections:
+3.3V: C1.2, C2.1, C3.2, C20.1, FB1.2, J1.9, TP2.1, U1.2 (DVDD), U1.3 (PVDD)
+3.3VA: C4.1, C5.2, C6.2, C7.1, C19.2, FB1.1, TP3.1, U1.16 (HPVDD), U1.17 (AVDD), U2.8 (V+)
GND: C1.1, C2.2, C3.1, C4.2, C5.1, C6.1, C7.2, C14.2, C15.2, C16.2, C17.2, C18.2, C19.1, C20.2, J1.1, J1.3, MIC1.2 (-), MIC2.2 (-), R9.2, R10.2, TP1.1, U1.4 (DGND), U1.13 (HPGND), U1.18 (AGND), U1.26 (CE), U1.29 (EPAD), U2.4 (V-), U2.9 (V-)
unnamed: C8.1, R1.2
unnamed: C9.2, R5.2, U2.7
unnamed: C10.2, R6.1, TP6.1, U2.1
unnamed: C11.1, R8.2
unnamed: C12.1, R7.2
unnamed: C13.1, R2.2
unnamed: J1.2, R12.1
unnamed: J1.4, R13.1
unnamed: J1.5, R14.1
unnamed: J1.6, R11.1
unnamed: J1.7, U1.27 (CDATA)
unnamed: J1.8, U1.28 (CCLK)
unnamed: C8.2, MIC1.1 (+), R9.1, TP8.1
unnamed: C13.2, MIC2.1 (+), R10.1
unnamed: C15.1, C16.1, U1.19 (ADCVREF)
unnamed: R14.2, U1.8 (ASDOUT)
unnamed: C10.1, TP7.1, U1.24 (LIN1)
unnamed: R13.2, U1.7 (LRCK)
unnamed: R11.2, U1.1 (MCLK)
unnamed: C9.1, U1.23 (RIN1)
unnamed: R12.2, U1.5 (SCLK)
unnamed: C14.1, U1.10 (VREF)
unnamed: R1.1, R3.1, TP5.1, U2.3 (+)
unnamed: R6.2, R7.1, U2.2 (-)
unnamed: R2.1, R4.1, U2.5 (+)
unnamed: R5.1, R8.1, U2.6 (-)
VMID: C11.2, C12.2, C17.1, C18.1, R3.2, R4.2, TP4.1, U1.20 (VMID)

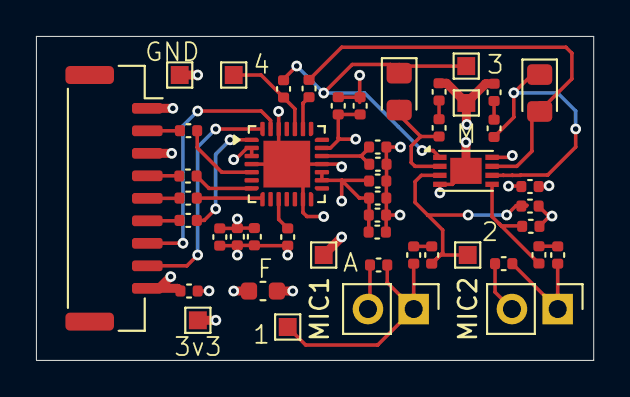
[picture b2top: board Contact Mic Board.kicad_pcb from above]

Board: 4 copper layers, 31.0 x 18.0 mm, 48 parts (0 on the bottom side), 30 nets.

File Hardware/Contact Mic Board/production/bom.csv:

Designator,Footprint,Quantity,Value,LCSC Part #
"C1, C16, C18, C19, C3, C5, C6",0402,7,0.1uF,
"C10, C13, C8, C9",0402,4,1uF,
"C11, C12",0402,2,470nF,
"C14, C15, C17, C2, C20, C4, C7",0402,7,10uF,
FB1,0603,1,FerriteBead_Small,
J1,JST_GH_SM09B-GHS-TB_1x09-1MP_P1.25mm_Horizontal,1,Conn_01x09_Pin,
"R1, R2",0402,2,47k,
"R10, R9",0402,2,1M,
"R11, R12, R13, R14",0402,4,33,
"R3, R4",0402,2,10M,
"R5, R6",0805,2,100k,
"R7, R8",0402,2,10K,
U1,QFN-28-1EP_4x4mm_P0.45mm_EP2.6x2.6mm,1,ES8388,
U2,DFN-8-1EP_3x2mm_P0.5mm_EP1.75x1.45mm,1,MCP6002-xMC,

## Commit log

2026-01-17 Add .gitignore
2026-01-24 Updated README.md from the default
2026-01-25 added native usb file retrieval
2026-01-25 updated README.md for USB file retrieval
2026-01-25 Added camera module, no functionality yet
2026-01-28 added 4mb flush, stereo mic input, gain constant, and comments for all functions
2026-02-01 split camera/OLED I2C, stabilize OV2640 MJPEG capture, and harden SD/video file handling
2026-02-02 Moved camera-related code into camera_ov2640.c, updated mic capture to its oown task, and added SD card mounting OLED error
2026-02-02 Updated README.md to include camera and cleaned it up
2026-03-06 received feedback from Andy + others and revised board
2026-03-10 submitted for manufacturinng. Flipped contact mic connections on main board to be aligned with contact mic board
2026-03-11 fixed power button and via proximity to pad on main board
2026-04-02 Add custom board pin remap and bring-up logging
2026-04-02 identified pin issue, buzzer conflicted with oled. camera vsync and pclck were bridged. Fixed both hardware bugs.
2026-04-02 Remap custom board GPIOs for SD, camera, mic, OLED, and button; remove buzzer code; disable BLE duplicate filtering
2026-04-08 began board migration to newer integrated camera 24 pin connector, NOT FINISHED
2026-04-14 added OLED failure handling, added event/error logs to txt files(not working as expected). added boot reset-cause display on oled. Disabled BLE scanning for testing, and that appears to be what stopp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
2026-04-14 added stereo mic recording, tested working
2026-04-14 Re-enable BLE trigger scanning and reduce passive scan duty cycle from 100% (10 ms every 10 ms) to 25% (10 ms every 40 ms), while keeping duplicate filtering off and preserving the custom UUID trigge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
2026-04-17 Update Hardware folder backups for contact mic and main board
2026-04-17 added ov2640 footprint
2026-04-18 found the schematics
2026-04-18 ov2640 footprints
2026-04-20 finished ov2640 schematic
2026-04-20 camera pcb
2026-04-20 Add contact mic debug mode that scans the shared I2C bus, retries ES8388 codec initialization until it comes up, shows retry/status updates on the OLED, and records a left-only mono WAV test capture 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
2026-04-22 Integrate contact mic into recording flow and initialize ES8388 once at boot
2026-04-25 Document contact mic workflow and clarify post-record OLED status
2026-04-26 finished camera pcb
2026-04-30 reviewed kevin's layout, changed boot reset buttons and updated layout
2026-05-01 Reduced Bluetooth duty cycle, added contact mic autosave, and reduced SD card burstiness
2026-05-01 Fix contact timestamp naming and lower camera FPS for stability
2026-05-06 Improve recording stop diagnostics and add contact codec boot settle delay
    Show explicit OLED stop reasons instead of silently falling back to Ready, including BLE stop, button stop, mic read/write/flush/seek failures, and contact mic failure stages.
    Add standard-mic stage tracking and check write/flush/seek failures so SD card write problems surface as recorder errors instead of being ignored.
    Add a 500 ms boot-settle delay before the first ES8388 initialization attempt while keeping the existing retry logic, so codec power and bias nodes have time to settle before the first register write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
2026-05-07 fixed data 0 and data 1 no connect issue, data pins for camera start at D2-D9
2026-05-08 fixed drc issues
2026-05-09 Reviewed Hardware for final submission, picked components
2026-05-11 Pull hardware updates from codex temp branch
    Bring the main board hardware changes from origin/codex-temp-main-hardware-push onto main while excluding transient KiCad autosave and lock files.
2026-05-12 submitted for manufacturing
2026-05-13 Mitigate contact-audio stalls and stop runaway camera recording
    Diagnosis: long recordings were showing a pattern where both audio files stopped well before the video file, followed later by INT_WDT resets. That pointed to an audio-side stall rather than a clean 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
    Mitigations in this commit: increase audio autosave interval from 3 s to 10 s, stagger contact autosave by 5 s so the two WAV header updates do not collide, remove periodic fsync() from mid-record au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
2026-05-13 Add OLED error log if there's no SD card
2026-05-20 Add segmented auto-restart for stalled recordings
    Detect mic and contact-mic stalls in the existing triple-task recorder and recover by rolling the session into a new segment instead of ending the overall recording. The restart path now preserves cu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
    Implement a strict 8-character filename stem for segmented sessions: DDHHMMXY when a BLE timestamp is available, and a zero-padded 6-digit session index plus type and segment when it is not. X select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
